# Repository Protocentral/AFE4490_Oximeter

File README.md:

ProtoCentral AF4490-based Pulse-oximeter shield for Arduino
================================
[Dont have it yet? Buy one here: ProtoCentral AFE4490 Pulse Oximeter Shield for Arduino – v2 (PC-MED-0406)](https://protocentral.com/product/protocentral-afe4490-pulse-oximeter-shield-for-arduino-v2/)

[Dont have it yet? Buy one here: ProtoCentral AFE4490 Pulse Oximeter Breakout Board Kit (PC-MED-0405)](https://protocentral.com/product/protocentral-afe4490-pulse-oximeter-breakout-board-kit/)

### If you're looking for the Arduino library, it's now moved here: https://github.com/Protocentral/protocentral-afe4490-arduino

This pulse oximetry shield from ProtoCentral uses the AFE4490 IC to enble your Arduino to measure heart rate as well as SpO2 values.
Pulse oximetry is an indirect method of measuring the oxygen levels in the blood. The sensor measures the skin's absorbance of red and IR light wavelengths to calculate the oxygen levels. The measurement is done by a probe that clips on to a finger and contains emitters as well as a light sensor.
Since the amount of blood flowing through any blood vessel varies (pulses) with the rate of blood from the heart, this can also be used for measuring heartrate without the need for connecting any ECG electrodes. 
Used along with Brainbay, this shield can display the real-time PPG as well as heart-rate values in addition to SpO2.

Features:
* TI AFE4490 Single chip pulse pulsoximetry front-end IC
* Standard Nellcor compatible DB7 connector for probe
* Calculates Spo2 values with provided code
* Real-time display of PPG (Photoplethysmogram)

## Includes:
----------
* 1x ProtoCentral Pulse Oximetry shield for Arduino
* 1x Set of stackable Arduino headers
* 1x "Nellcor compatible" Pulse oximetry finger probe. 

## Repository Contents
-------------------
* **/arduino** - Arduino library and example sketch
* **/hardware** - All Eagle design files (.brd, .sch)
* **/extras** - datasheets and extras
* **/processing** - Processing-based Application

## Connecting the shield to your Arduino
-------------------------------------
 Connect the ECG/Respiration shield to the Arduino by stacking it on top of your Arduino. This shield uses the SPI interface  to communicate with the Arduino. Since this includes the ICSP header, which is used on newer Arduinos for SPI communication,  this shield is also compatible newer Arduino boards such as the Arduino Yun and Due.

## The Arduino library for this is now available here: https://github.com/Protocentral/protocentral-afe4490-arduino

## Wiring the Breakout to your Arduino
------------------------------------
 If you have bought the breakout the connection with the Arduino board is as follows:
 
|AFE4490 pin label| Arduino Connection   |Pin Function                  |
|----------------- |:--------------------:|-----------------:           |
| GND              | Gnd                  |  Gnd                        |             
| DRDY             | D2                   |  Data ready(interrupt)      |
| MISO             | D12                  |  Slave out                  |
| SCK              | D13                  |  SPI clock                  |
| MOSI             | D11                  |  Slave in                   |
| CS0              | D7                   |  Slave select               |
| START            | D5                   |  Conversion start Pin       |
| PWDN             | D4                   |  Power Down/ Reset          |
| DIAG_END         | NC                   |  Diagnostic output          |
| LED_ALM          | NC                   |  Cable fault indicator      |
| PD_ALM           | NC                   |  PD sensor fault indicator  |
| VCC              | +5v                  |  Supply voltage             |

## Using Processing - Data Visualization Software
----------------------------------------------
 Processing is a data visualization software, in existence since 2001, used by artists and scientists alike. It’s an open source coding framework based on Java. If you are familiar with the Arduino environment, the Processing IDE is similar and you won’t have much of a learning curve to climb!
 
 The following are the steps to run the code:

### 1. Download and Install Processing 

 Download the processing ide latest version from the link

* [Download Processing for your OS] (http://download.processing.org/)

Once downloaded, unzip the archive and install the app as per your OS.

### 2. Download the Processing code for Pulse Oximeter visualization

 a. Download the necessary files & directories or clone to your desktop from GitHub.

 b. Unzipping the archive should make a folder by name AFE4490 Oximeter Shield that contains the visualization code.

 c. Locate the Processing sketchbook directory on your computer. This should have been created automatically when you installed processing. Depending on your operating system, the path will be as follows:

* On Windows: c:/My Documents/Processing/
* On MAC: /Users/your_user_name/Documents/Processing/
* On Linux: /Home/your_user_name/sketchbook/

**Note:** This directory appears as "Processing" on Windows/Mac, and goes by the name "Sketchbook" on Linux. Create a subdirectory by name "libraries" if one doesn't exist already.

 d. From the above mentioned "AFE4490_Oximeter-master" directory Copy/Move the contents of the AFE4490_Oximeter-master/processing/openview_pulseox folder to the Processing sketchbook directory which is also mentioned above (Locate the Processing sketchbook)

 e. Finally, copy the G4P directories from AFE4490_Oximeter-master\Processing\libraries and paste them into the libraries directory of your Processing sketchbook.

 f. You are all set now to get your first PPG wave form and SpO2 reading visualized from the AFE4490 Oximeter Shield!

### 3. Uploading Arduino Sketch For AFE4490 Oximeter Shield

 a. Open the Arduino IDE to load the embedded code for AFE4490 Oximeter Shield.

 b. Click on File -> Open and Browse the .ino code for Arduino from AFE4490_Oximeter-master\arduino and export the application to Arduino.

### 4. Open Processing & launch the ces_view_oximeter

 a. If Processing IDE was open, close it and reopen to refresh the libraries and sketches. The repositories are not refreshed if the IDE was open while the Sketches and Libraries were being updated.

 b. Double-click any of the .pde files in the openview_pulseox directory to open all of the pulse oximeter code in the Processing IDE.

 c. If everything done so far was good, clicking the "run" button on the top left corner of the IDE, should run the code! If it does not, make sure you installed your libraries correctly.

 d. Once the GUI is running, select the port connect with pulse oximeter shield from the "SELECT PORT" dropdown as shown in the figure below

 e. Once the port selection is appropriate the START button gets enabled. Click "START" to initiate visualization

 f. You should see the PPG ( RED and IR) waves generated with the values obtained from the AFE4490 Oximeter Shield Breakout Board as shown below.

License Information
===================

This product is open source! Both, our hardware and software are open source and licensed under the following licenses:

Hardware
---------

**All hardware is released under [Creative Commons Share-alike 4.0 International](http://creativecommons.org/licenses/by-sa/4.0/).**

You are free to:

* Share — copy and redistribute the material in any medium or format
* Adapt — remix, transform, and build upon the material for any purpose, even commercially.
The licensor cannot revoke these freedoms as long as you follow the license terms.

Under the following terms:

* Attribution — You must give appropriate credit, provide a link to the license, and indicate if changes were made. You may do so in any reasonable manner, but not in any way that suggests the licensor endorses you or your use.
* ShareAlike — If you remix, transform, or build upon the material, you must distribute your contributions under the same license as the original.

Software
--------

**All software is released under the MIT License(http://opensource.org/licenses/MIT).**

THE SOFTWARE IS PROVIDED "AS IS", WITHOUT WARRANTY OF ANY KIND, EXPRESS OR IMPLIED, INCLUDING BUT NOT LIMITED TO THE WARRANTIES OF MERCHANTABILITY, FITNESS FOR A PARTICULAR PURPOSE AND NONINFRINGEMENT. IN NO EVENT SHALL THE AUTHORS OR COPYRIGHT HOLDERS BE LIABLE FOR ANY CLAIM, DAMAGES OR OTHER LIABILITY, WHETHER IN AN ACTION OF CONTRACT, TORT OR OTHERWISE, ARISING FROM, OUT OF OR IN CONNECTION WITH THE SOFTWARE OR THE USE OR OTHER DEALINGS IN THE SOFTWARE.

Please check [*LICENSE.md*](LICENSE.md) for detailed license descriptions.

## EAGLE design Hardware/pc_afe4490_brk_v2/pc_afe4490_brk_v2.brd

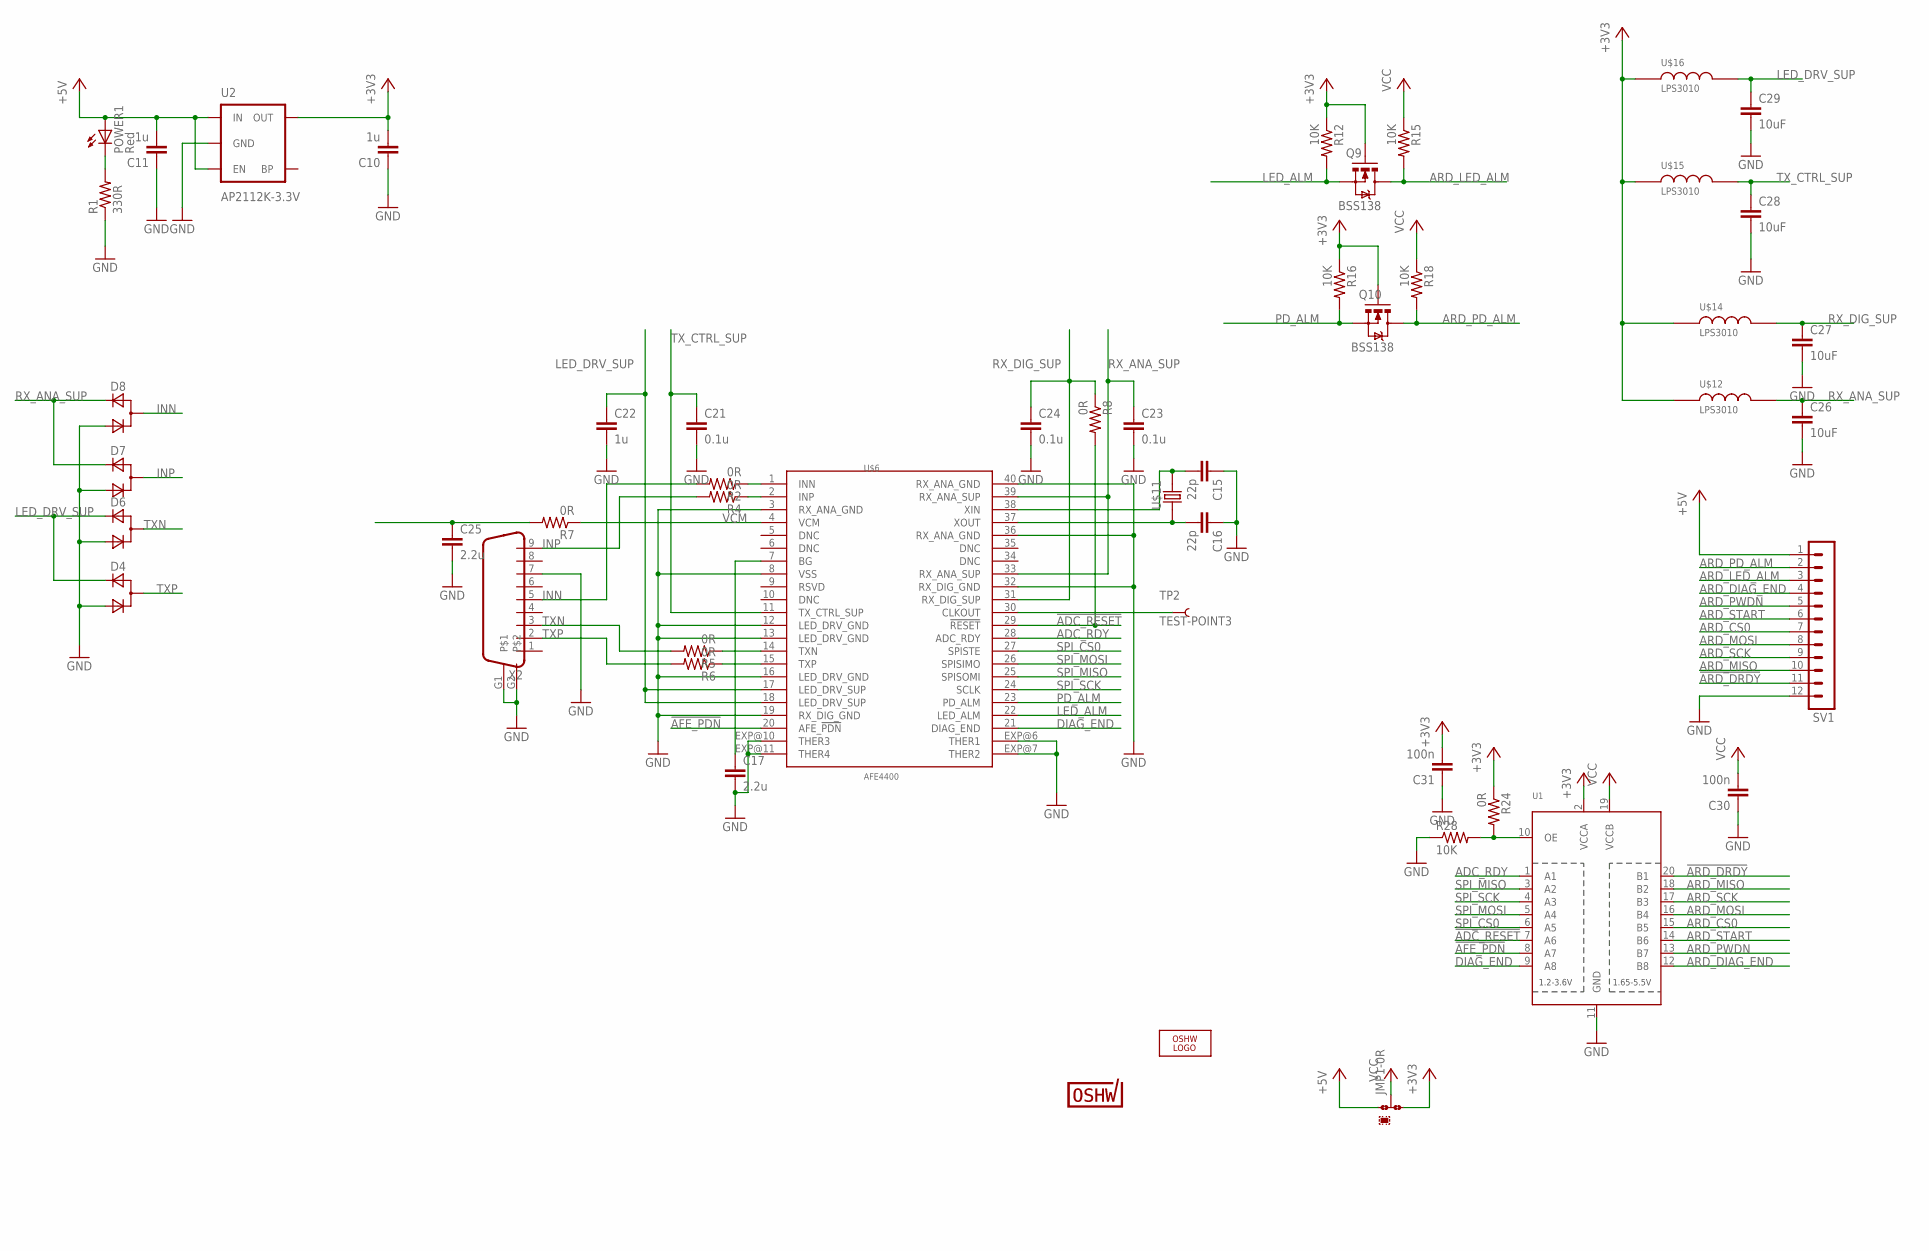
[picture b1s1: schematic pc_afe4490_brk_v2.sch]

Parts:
C10, C11, C22: 1u; C0805
C15, C16: 22p; C0402
C17, C25: 2.2u; C0402
C21, C23, C24: 0.1u; C0805
C26, C27, C28, C29: 10uF; C0805
C30, C31: 100n; C0402
D4, D6, D7, D8: D_ACACSOT323; SOT323
JMP1: 0R-JUMPA; A0R-JMP
LOGO2: OSHW_LOGO_FILLX0200-NT; OSHW_FILLX200_NOTEXT
POWER1: Red; CHIPLED_0603
Q9, Q10: BSS138; SOT23-3
R1: 330R; R0805
R2, R4, R7: 0R; R0402
R5, R6, R8: 0R; R0805
R12, R15, R16, R18, R28: 10K; 0805
R24: 0R; 0805
SV1: MA12-1
TP2: TEST-POINT3; PAD.03X.03
U1: TXB0108PWR; TSSOP20
U2: AP2112K-3.3V; SOT23-5
U$1: PROTY-LOGO; LOGO-PROTY
U$3: PROTY_LOGO_WITH_TEXT; PROTY_WITH_TEXT
U$4: CERT-SMALL; CERT-SMALL-SILK
U$6: AFE4400; QFN-40
U$11: ABM3
U$12, U$14, U$15, U$16: LPS3010; LPS
X2: DB9

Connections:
!ADC_RESET: R8.2, U1.7 (A6), U$6.29 (!RESET)
!AFE_PDN: U1.8 (A7), U$6.20 (AFE_!PDN)
!ARD_DRDY: SV1.11, U1.20 (B1)
+3V3: C10.2, C31.2, JMP1.3, Q9.1 (G), Q10.1 (G), R12.1, R16.1, R24.1, U1.2 (VCCA), U2.5 (OUT), U$12.1, U$14.1, U$15.1, U$16.1
+5V: C11.2, JMP1.1, POWER1.A, SV1.1, U2.1 (IN), U2.3 (EN)
ADC_RDY: U1.1 (A1), U$6.28 (ADC_RDY)
ARD_CS0: SV1.7, U1.15 (B5)
ARD_DIAG_END: SV1.4, U1.12 (B8)
ARD_LED_ALM: Q9.3 (D), R15.2, SV1.3
ARD_MISO: SV1.10, U1.18 (B2)
ARD_MOSI: SV1.8, U1.16 (B4)
ARD_PD_ALM: Q10.3 (D), R18.2, SV1.2
ARD_PWDN: SV1.5, U1.13 (B7)
ARD_SCK: SV1.9, U1.17 (B3)
ARD_START: SV1.6, U1.14 (B6)
DIAG_END: U1.9 (A8), U$6.21 (DIAG_END)
GND: C10.1, C11.1, C15.1, C16.1, C17.2, C21.2, C22.2, C23.2, C24.2, C25.2, C26.2, C27.2, C28.2, C29.2, C30.1, C31.1, D4.2 (C), D6.2 (C), D7.2 (C), D8.2 (C), R1.1, R28.1, SV1.12, U1.11 (GND), U2.2 (GND), U$6.3 (RX_ANA_GND), U$6.8 (VSS), U$6.12 (LED_DRV_GND), U$6.13 (LED_DRV_GND), U$6.16 (LED_DRV_GND), U$6.19 (RX_DIG_GND), U$6.32 (RX_DIG_GND), U$6.36 (RX_ANA_GND), U$6.40 (RX_ANA_GND), U$6.EXP@6 (THER1), U$6.EXP@7 (THER2), U$6.EXP@10 (THER3), U$6.EXP@11 (THER4), X2.7, X2.G1, X2.G2
INN: D8.1 (CA), R2.2, X2.5
INP: D7.1 (CA), R4.2, X2.9
LED_ALM: Q9.2 (S), R12.2, U$6.22 (LED_ALM)
LED_DRV_SUP: C22.1, C29.1, D4.3 (A), D6.3 (A), U$6.17 (LED_DRV_SUP), U$6.18 (LED_DRV_SUP), U$16.2
unnamed: POWER1.C, R1.2
unnamed: C15.2, U$6.38 (XIN), U$11.2
unnamed: C16.2, U$6.37 (XOUT), U$11.1
unnamed: C17.1, U$6.7 (BG)
unnamed: TP2.P$1, U$6.30 (CLKOUT)
unnamed: R2.1, U$6.1 (INN)
unnamed: R4.1, U$6.2 (INP)
unnamed: R5.1, U$6.14 (TXN)
unnamed: R6.1, U$6.15 (TXP)
unnamed: C25.1, R7.2
OE: R24.2, R28.2, U1.10 (OE)
PD_ALM: Q10.2 (S), R16.2, U$6.23 (PD_ALM)
RX_ANA_SUP: C23.1, C26.1, D7.3 (A), D8.3 (A), U$6.33 (RX_ANA_SUP), U$6.39 (RX_ANA_SUP), U$12.2
RX_DIG_SUP: C24.1, C27.1, R8.1, U$6.31 (RX_DIG_SUP), U$14.2
SPI_CS0: U1.6 (A5), U$6.27 (SPISTE)
SPI_MISO: U1.3 (A2), U$6.25 (SPISOMI)
SPI_MOSI: U1.5 (A4), U$6.26 (SPISIMO)
SPI_SCK: U1.4 (A3), U$6.24 (SCLK)
TXN: D6.1 (CA), R5.2, X2.3
TXP: D4.1 (CA), R6.2, X2.2
TX_CTRL_SUP: C21.1, C28.1, U$6.11 (TX_CTRL_SUP), U$15.2
VCC: C30.2, JMP1.2, R15.1, R18.1, U1.19 (VCCB)
VCM: R7.1, U$6.4 (VCM)

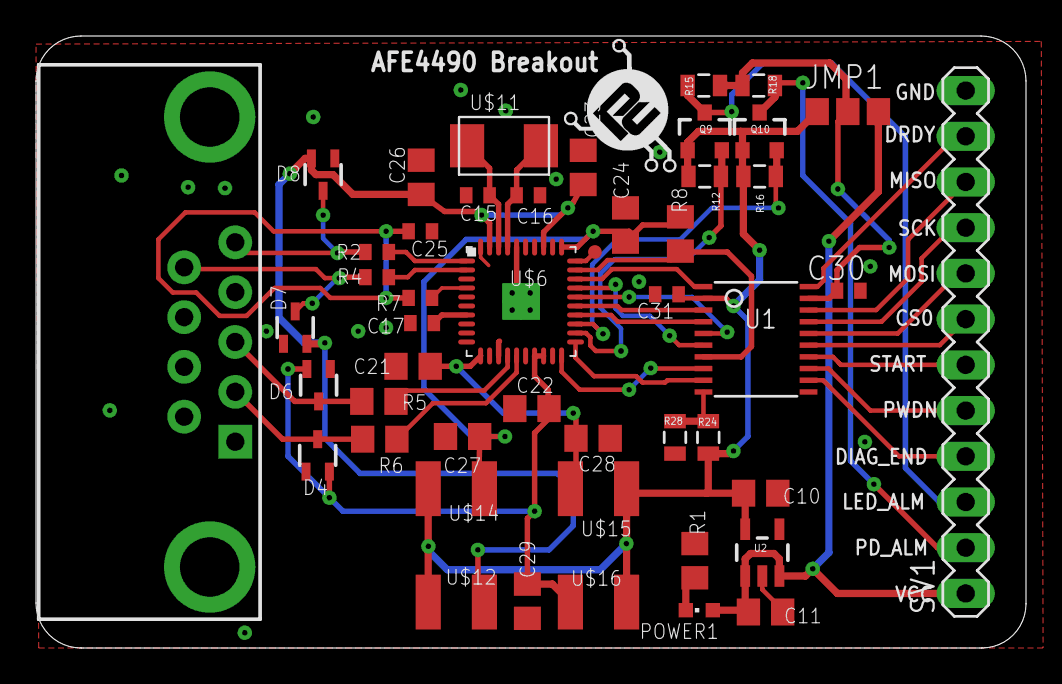
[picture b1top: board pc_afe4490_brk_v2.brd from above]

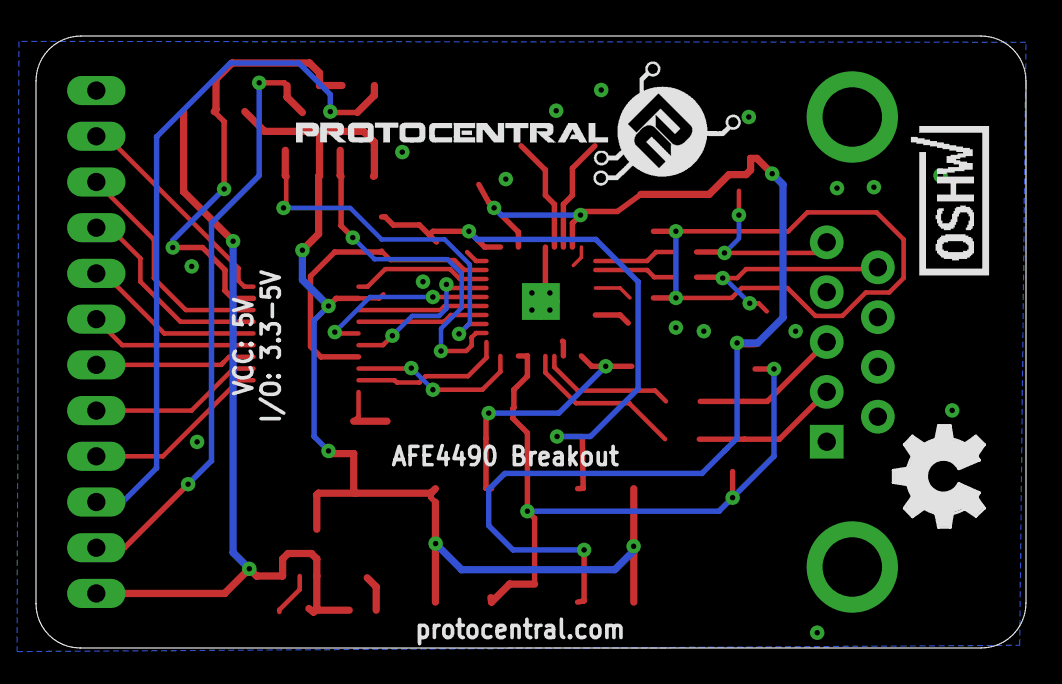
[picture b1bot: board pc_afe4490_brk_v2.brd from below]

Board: 4 copper layers, 55.0 x 34.0 mm, 52 parts (3 on the bottom side), 44 nets.

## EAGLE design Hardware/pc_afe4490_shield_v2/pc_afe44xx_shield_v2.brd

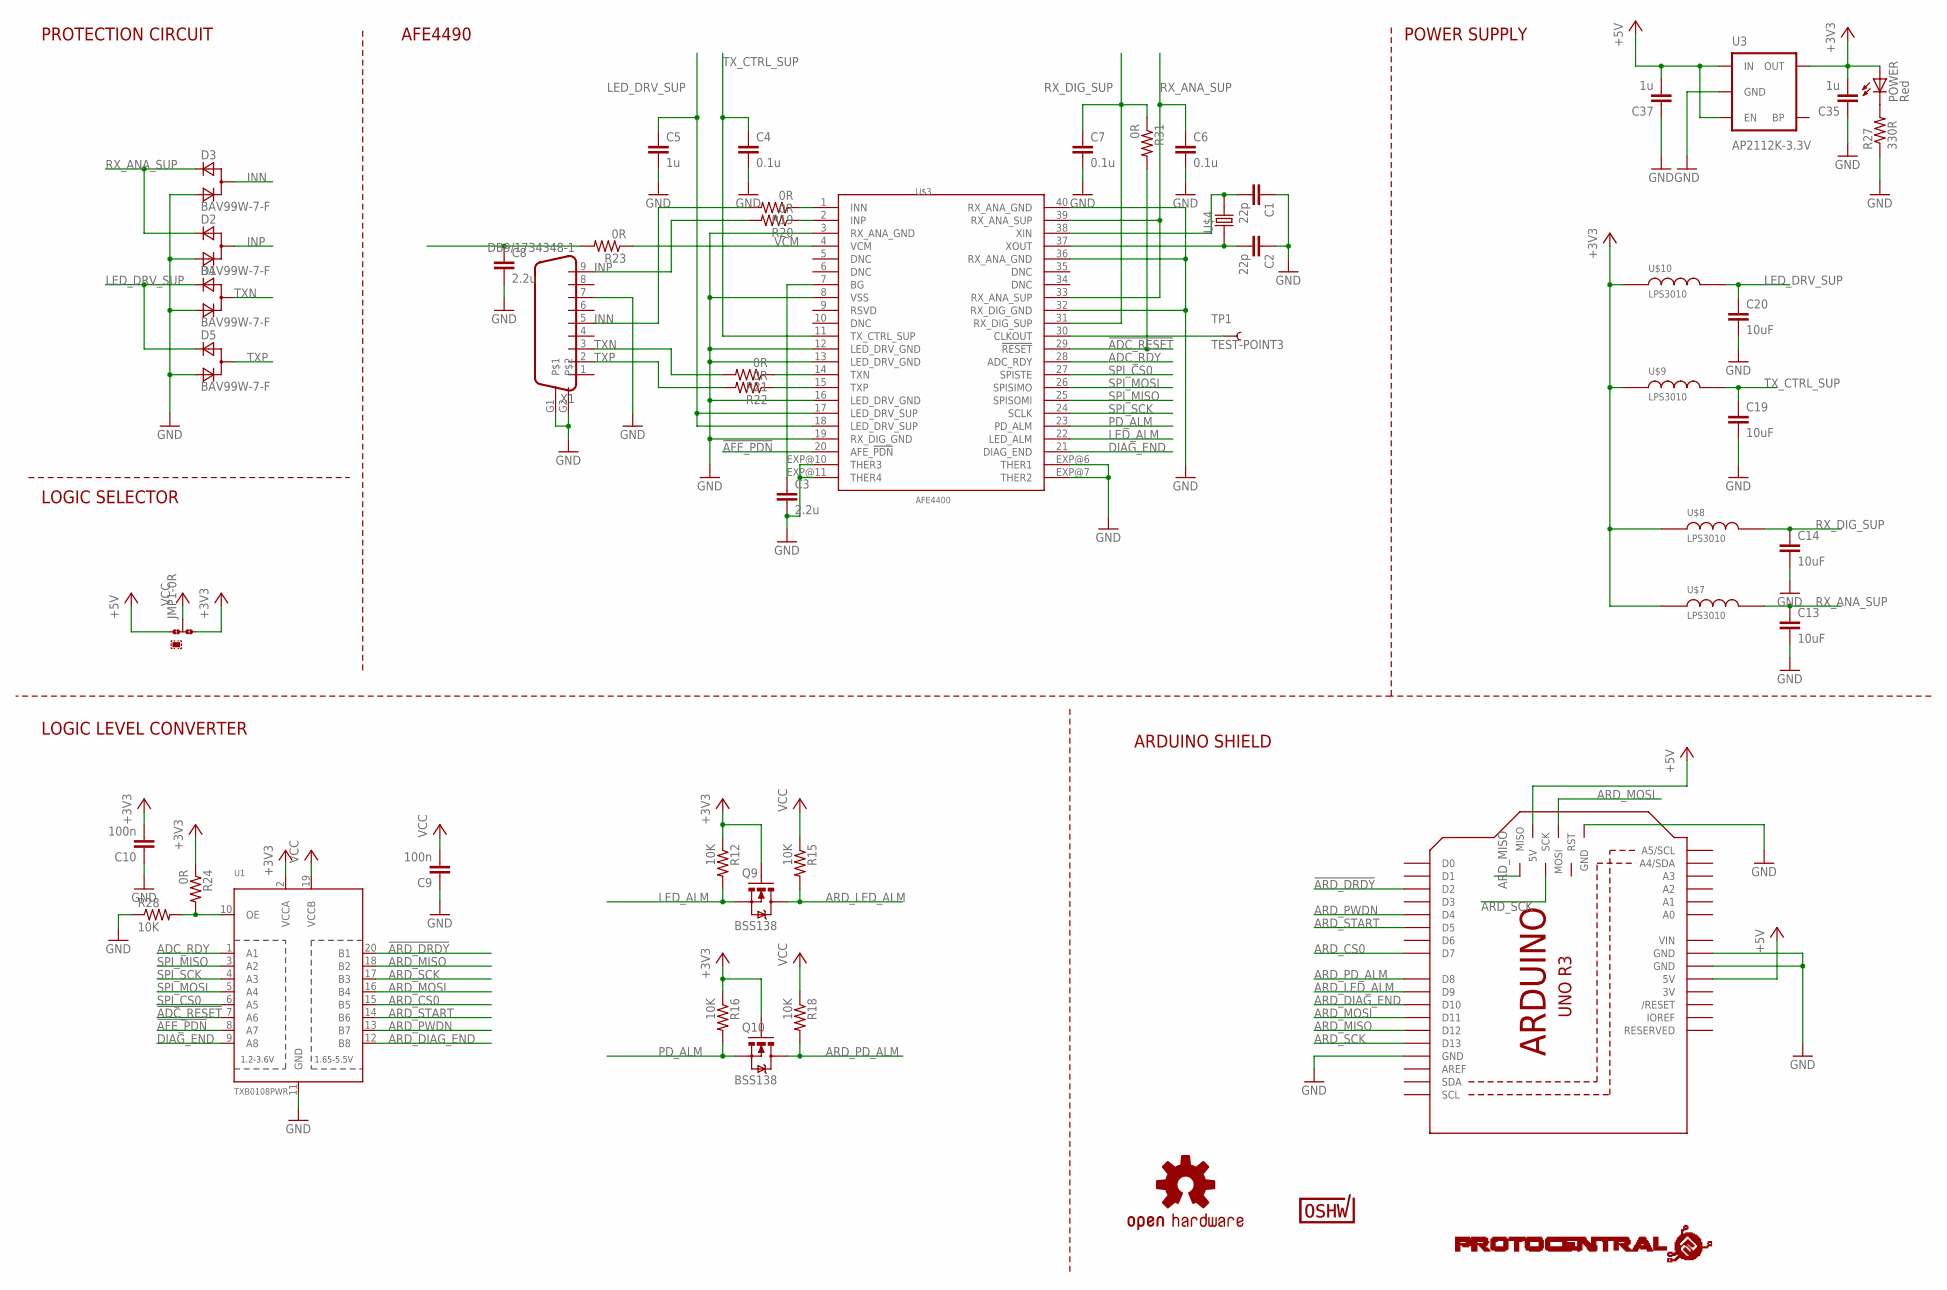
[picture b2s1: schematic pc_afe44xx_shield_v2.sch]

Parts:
C1, C2: 22p; C0402
C3, C8: 2.2u; C0402
C4, C6, C7: 0.1u; C0805
C5, C35, C37: 1u; C0805
C9, C10: 100n; C0402
C13, C14, C19, C20: 10uF; C0805
D1, D2, D3, D5: BAV99W-7-F; SOT323
JMP1: 0R-JUMPA; A0R-JMP
M1: ARDUINO
POWER: Red; CHIPLED_0603
Q9, Q10: BSS138; SOT23-3
R12, R15, R16, R18, R28: 10K; 0805
R19, R20, R23: 0R; R0402
R21, R22, R31: 0R; R0805
R24: 0R; 0805
R27: 330R; R0805
TP1: TEST-POINT3; PAD.03X.03
U1: TXB0108PWR; TSSOP20
U3: AP2112K-3.3V; SOT23-5
U$3: AFE4400; QFN-40
U$4: ABM3
U$5: PROTY_LOGO_WITH_TEXT; PROTY_WITH_TEXT
U$6: CERT-SMALL; CERT-SMALL-SILK
U$7, U$8, U$9, U$10: LPS3010; LPS
U$11: OSHW-LOGOM; OSHW-LOGO-M
X1: DB9/1734348-1; DB9

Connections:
3V: M1.3V
!ADC_RESET: R31.2, U1.7 (A6), U$3.29 (!RESET)
!AFE_PDN: U1.8 (A7), U$3.20 (AFE_!PDN)
!ARD_DRDY: M1.D2, U1.20 (B1)
+3V3: C10.2, C35.2, JMP1.3, POWER.A, Q9.1 (G), Q10.1 (G), R12.1, R16.1, R24.1, U1.2 (VCCA), U3.5 (OUT), U$7.1, U$8.1, U$9.1, U$10.1
+5V: C37.2, JMP1.1, M1.5V, M1.5V_ICSP (5V), U3.1 (IN), U3.3 (EN)
ADC_RDY: U1.1 (A1), U$3.28 (ADC_RDY)
ARD_CS0: M1.D7, U1.15 (B5)
ARD_DIAG_END: M1.D10, U1.12 (B8)
ARD_LED_ALM: M1.D9, Q9.3 (D), R15.2
ARD_MISO: M1.D12, M1.MISO, U1.18 (B2)
ARD_MOSI: M1.D11, M1.MOSI, U1.16 (B4)
ARD_PD_ALM: M1.D8, Q10.3 (D), R18.2
ARD_PWDN: M1.D4, U1.13 (B7)
ARD_SCK: M1.D13, M1.SCK, U1.17 (B3)
ARD_START: M1.D5, U1.14 (B6)
DIAG_END: U1.9 (A8), U$3.21 (DIAG_END)
GND: C1.1, C2.1, C3.2, C4.2, C5.2, C6.2, C7.2, C8.2, C9.1, C10.1, C13.2, C14.2, C19.2, C20.2, C35.1, C37.1, D1.2 (C), D2.2 (C), D3.2 (C), D5.2 (C), M1.GND, M1.GND@1 (GND), M1.GND@2 (GND), M1.GND@3 (GND), R27.1, R28.1, U1.11 (GND), U3.2 (GND), U$3.3 (RX_ANA_GND), U$3.8 (VSS), U$3.12 (LED_DRV_GND), U$3.13 (LED_DRV_GND), U$3.16 (LED_DRV_GND), U$3.19 (RX_DIG_GND), U$3.32 (RX_DIG_GND), U$3.36 (RX_ANA_GND), U$3.40 (RX_ANA_GND), U$3.EXP@6 (THER1), U$3.EXP@7 (THER2), U$3.EXP@10 (THER3), U$3.EXP@11 (THER4), X1.7, X1.G1, X1.G2
INN: D3.1 (CA), R19.2, X1.5
INP: D2.1 (CA), R20.2, X1.9
LED_ALM: Q9.2 (S), R12.2, U$3.22 (LED_ALM)
LED_DRV_SUP: C5.1, C20.1, D1.3 (A), D5.3 (A), U$3.17 (LED_DRV_SUP), U$3.18 (LED_DRV_SUP), U$10.2
unnamed: C3.1, U$3.7 (BG)
unnamed: R21.1, U$3.14 (TXN)
unnamed: TP1.P$1, U$3.30 (CLKOUT)
unnamed: R22.1, U$3.15 (TXP)
unnamed: POWER.C, R27.2
unnamed: R19.1, U$3.1 (INN)
unnamed: C8.1, R23.2
unnamed: C1.2, U$3.38 (XIN), U$4.2
unnamed: C2.2, U$3.37 (XOUT), U$4.1
unnamed: R24.2, R28.2, U1.10 (OE)
unnamed: R20.1, U$3.2 (INP)
PD_ALM: Q10.2 (S), R16.2, U$3.23 (PD_ALM)
RX_ANA_SUP: C6.1, C13.1, D2.3 (A), D3.3 (A), U$3.33 (RX_ANA_SUP), U$3.39 (RX_ANA_SUP), U$7.2
RX_DIG_SUP: C7.1, C14.1, R31.1, U$3.31 (RX_DIG_SUP), U$8.2
SPI_CS0: U1.6 (A5), U$3.27 (SPISTE)
SPI_MISO: U1.3 (A2), U$3.25 (SPISOMI)
SPI_MOSI: U1.5 (A4), U$3.26 (SPISIMO)
SPI_SCK: U1.4 (A3), U$3.24 (SCLK)
TXN: D1.1 (CA), R21.2, X1.3
TXP: D5.1 (CA), R22.2, X1.2
TX_CTRL_SUP: C4.1, C19.1, U$3.11 (TX_CTRL_SUP), U$9.2
VCC: C9.2, JMP1.2, R15.1, R18.1, U1.19 (VCCB)
VCM: R23.1, U$3.4 (VCM)
VIN: M1.VIN

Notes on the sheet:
POWER SUPPLY
ARDUINO SHIELD
LOGIC LEVEL CONVERTER
LOGIC SELECTOR
PROTECTION CIRCUIT
AFE4490

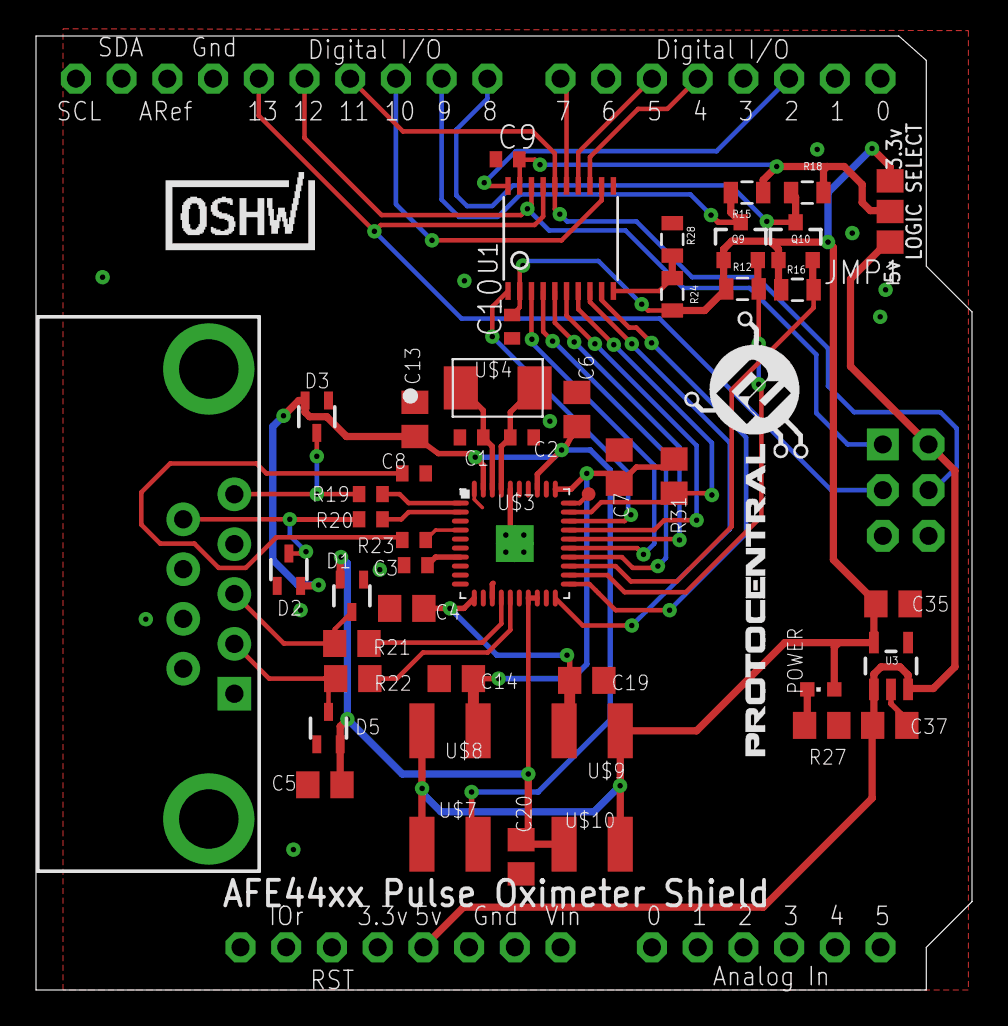
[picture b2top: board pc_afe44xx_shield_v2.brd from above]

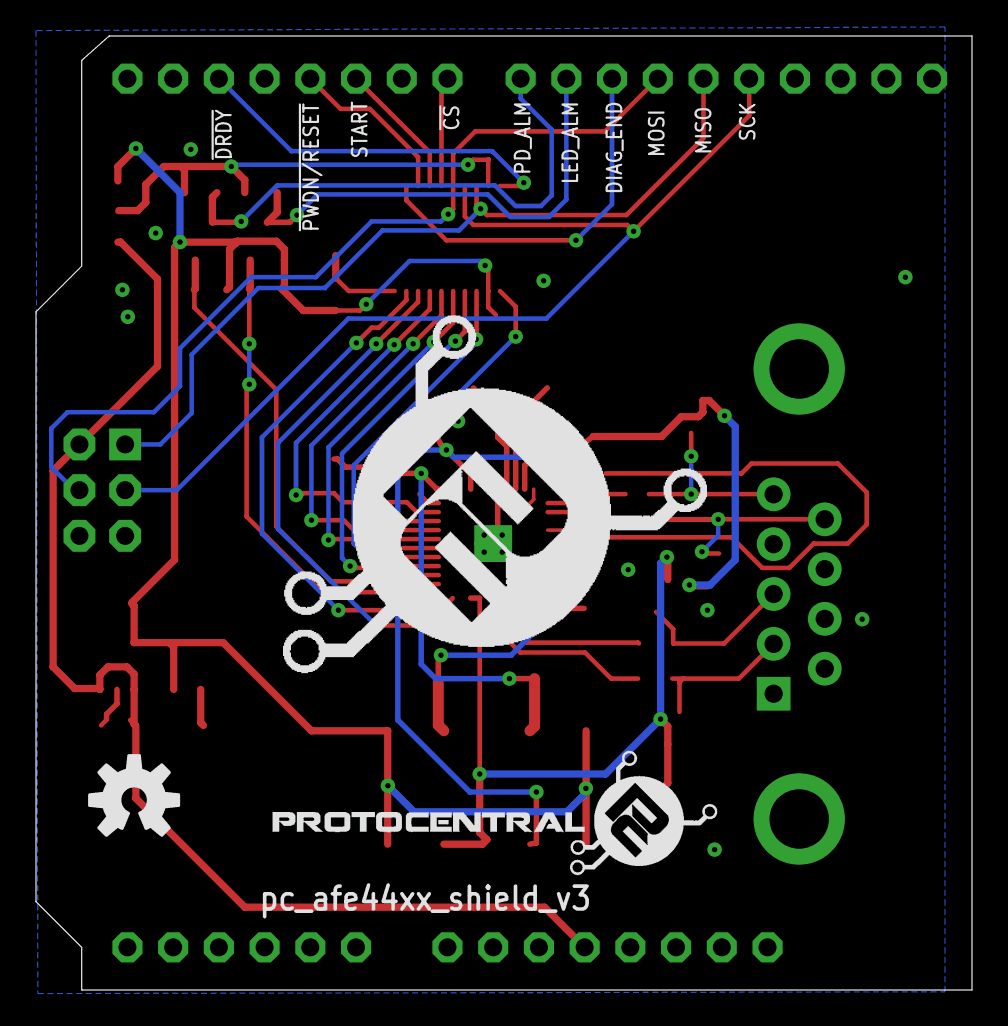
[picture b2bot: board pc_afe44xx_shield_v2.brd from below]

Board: 4 copper layers, 52.0 x 53.0 mm, 53 parts (3 on the bottom side), 44 nets.

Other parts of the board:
U$1: PROTY_WITH_TEXT
U$2: PROTY-LOGO-LARGE

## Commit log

2015-10-15 :circus_tent: Added .gitattributes & .gitignore files
2015-10-15 afe4400/4490 Oximeter
2015-10-15 SchematicDesignFile
2015-10-28 Datasheet and output
2015-10-28 Eagle file
2015-10-28 Source file and example sketch
2016-08-22 Processing Sketch
2016-08-22 Final Output Screenshots
2016-08-22 Processing Libraires
2016-08-23 Processing Ardunio Sketch
2016-08-23 Final Output
2016-10-21 Processing Code
2016-11-12 Update Readme, removed support for Brainbay
2016-11-13 Removed unused libraries and files
2016-11-13 Updated New Processing application
2016-11-18 Updated license information
2016-11-29 updated sketch
2016-11-29 updated pictures
2016-12-29 updated schematic
2017-01-19 Updated schematics for v2 breakout and shield
2017-01-20 Fixed the j1, j2 use error for supporting Arduino SAMD boards
2017-06-06 Averages all values in the spo2_array, without skipping the first 50.
2017-06-06 Fix interpretation order of the IR and RED values from Arduino, giving a correct result for (RedAC/abs(RedDC))/(IrAC/abs(IrDC)).
2017-08-16 Added algorithm for % SpO2 calculation
2017-08-16 Added algorithm for SpO2 % calculation
2017-08-22 added algorithm for SpO2 calculation
2018-04-01 Updated Reset pin config in firmware
    Corrected bug in software for RESET pin handling
2019-03-27 Updated Afe4490
2020-12-26 Update library information
2020-12-26 Correct image paths

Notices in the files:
README.md:
CC-BY-SA-4.0
parts and their libraries:
SparkFun-PowerIC: Licensing: Creative Commons ShareAlike 4.0 International - https://creativecommons.org/licenses/by-sa/4.0
